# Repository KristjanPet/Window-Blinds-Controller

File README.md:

> [!NOTE]
> This is the first hardware version of the project. Both the PCB and mechanical design are relatively bulky; a second revision is in development with the goal of reducing the overall size by approximately 80%.
>
> Contributions, design ideas, and improvement suggestions are more than welcome.

# Window Blinds Controller

ESP32-S3 based embedded controller for motorized window blinds, built with C++/ESP-IDF, TMC2209 stepper control, FreeRTOS event-driven architecture, MQTT integration, custom KiCad PCB, and custom mechanical parts.

## What this project demonstrates

- Embedded C++ architecture using separated modules and interfaces
- ESP32-S3 firmware development with ESP-IDF and PlatformIO
- FreeRTOS task-based design with a central command/event queue
- Stepper motor control using RMT pulse generation and PCNT position tracking
- TMC2209 UART driver configuration and DIAG/stall event handling
- Homing, calibration, soft limits, stall recovery, and fault-state handling
- MQTT-based smart-home command interface
- Unit testing with PlatformIO/Unity and fake hardware abstractions
- Custom KiCad schematic and PCB design
- Custom mechanical design: CNC aluminium motor/rope holder and 3D printed enclosure
- Doxygen API documentation
- Project planning using Jira and draw.io diagrams

---

## Hardware

Main components:

| Component | Purpose |
|---|---|
| ESP32-S3 | Main MCU, Wi-Fi, FreeRTOS firmware |
| TMC2209 | Stepper motor driver with UART configuration and DIAG/stall signal |
| Nema 17 Stepper motor | Blind movement |
| NJK-5002C Home/reference sensor | Calibration and homing |
| Wall buttons | Local manual control |
| Custom PCB | Power, MCU, driver, sensor, and connector integration |

## Mechanical design

The project also includes custom mechanical parts:

- CNC aluminium motor and rope holder for the blind mechanism
- 3D printed front/back mounting holders for aluminium
- 3D printed electronics case
- 3D printed cover
- CAD models and exported STL/STEP files

## Documentation and planning

- Doxygen configuration for generated C++ API documentation
- draw.io diagrams for system architecture and firmware flow
- Jira used for task planning, issue tracking, and development organization

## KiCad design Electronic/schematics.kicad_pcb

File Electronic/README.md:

# Electronics Hardware

This folder contains the PCB and electronics design files for the window blinds controller.

The electronics are built around an ESP32-S3 development board, a TMC2209 stepper motor driver, a 12 V to 5 V buck converter, input protection, button/sensor connectors, and dual-inverter Schmitt-trigger input paths.

## Schematics

## Main electronics

| Component                  | Qty | Value / Part                | Purpose                                                                 |
| -------------------------- | --: | --------------------------- | ----------------------------------------------------------------------- |
| ESP32-S3 development board |   1 | `ESP32-S3-DEVKITC-1-N16R8V` | Main MCU, firmware, Wi-Fi, MQTT, GPIO control                           |
| Stepper driver             |   1 | `TMC2209 SilentStepStick`   | Stepper motor driver with UART configuration and DIAG/StallGuard output |
| Buck converter             |   1 | 12 V to 3 V DC-DC buck      | Generates 3 V supply from the 12 V input                                |
| Schmitt trigger            |   1 | `74HC14`                    | Cleans three input signals with two inverter gates per signal            |
| TVS diode                  |   1 | `SMBJ15A`                   | 12 V input transient protection                                         |
| Polyfuse                   |   1 | 2 A                         | Input overcurrent protection                                            |

## Passive components

| Component type | Qty | Value  |
| -------------- | --: | ------ |
| Capacitors     |   4 | 100 nF |
| Capacitor      |   1 | 470 µF |
| Resistors      |   2 | 1 kΩ   |
| Resistors      |   3 | 10 kΩ  |
| Resistors      |   3 | 3.3 kΩ |

## Connectors

| Connector    | Qty | Purpose                                           |
| ------------ | --: | ------------------------------------------------- |
| 2-pin JST-XH |   1 | Power input                                       |
| 4-pin JST-XH |   1 | External wiring / motor-driver related connection |
| 3-pin JST-XH |   1 | External input buttons connection                  |
| 3-pin JST-XH |   1 | NJK-5002C home sensor connection                  |

## Conditioned input logic

Each external input passes through two gates of the 74HC14. The two inversions
cancel, so the ESP32-S3 sees the same logical polarity as the signal entering the
first gate. The final gate is a 3.3 V push-pull output, so the firmware keeps the
ESP32 internal pull resistors disabled.

| Input       | ESP32-S3 pin | Pre-Schmitt idle | Pre-Schmitt active | ESP32 idle | ESP32 active | Activation edge |
| ----------- | -----------: | ---------------: | -----------------: | ---------: | -----------: | --------------: |
| Up button   |     `GPIO12` |              LOW |               HIGH |        LOW |          HIGH |          Rising |
| Down button |     `GPIO13` |              LOW |               HIGH |        LOW |          HIGH |          Rising |
| Home sensor |     `GPIO14` |             HIGH |                LOW |       HIGH |           LOW |         Falling |

## External hardware

The PCB is designed to work with the following external hardware:

| Part                                           | Notes                                                |
| ---------------------------------------------- | ---------------------------------------------------- |
| 12 V, 3 A power supply adapter                 | Main power input for the controller and motor system |
| NEMA 17 stepper motor `17HS4401`               | Stepper motor used to drive the blinds mechanism     |
| GREATZT NJK-5002C Hall effect proximity sensor | Home/reference sensor for calibration                |

Before choosing the motor and power supply, the weight and friction of the specific blinds should be checked. Heavier blinds, tight mechanisms, or higher-friction rope systems may require more torque, different gearing, or a stronger motor/driver setup.

## Design notes

The current PCB uses development-board style modules for the ESP32-S3, TMC2209 SilentStepStick, and DC-DC buck converter.

This made the prototype easier to build and debug because those modules were available during development. If space is critical, these modules could be replaced with direct SMD implementations in a future PCB revision.

Possible future optimizations:

* replace ESP32-S3 DevKit with the ESP32-S3 module (or any other not so overpowerd ESP) directly on the PCB
* replace TMC2209 SilentStepStick with the bare TMC2209 IC and required support components
* replace the buck converter module with an onboard SMD regulator circuit
* reduce connector size or move connectors based on the final enclosure
* optimize PCB shape for the mechanical case

## Safety note

This board controls a motorized mechanism. Before installation, verify:

* correct supply voltage and polarity
* current rating of the power adapter
* stepper motor current settings
* fuse/protection behavior
* connector wiring
* home sensor behavior
* motor direction
* stall detection
* mechanical end stops

Do not operate the blinds unattended until calibration, stall detection, and fault handling have been tested on the real mechanism.

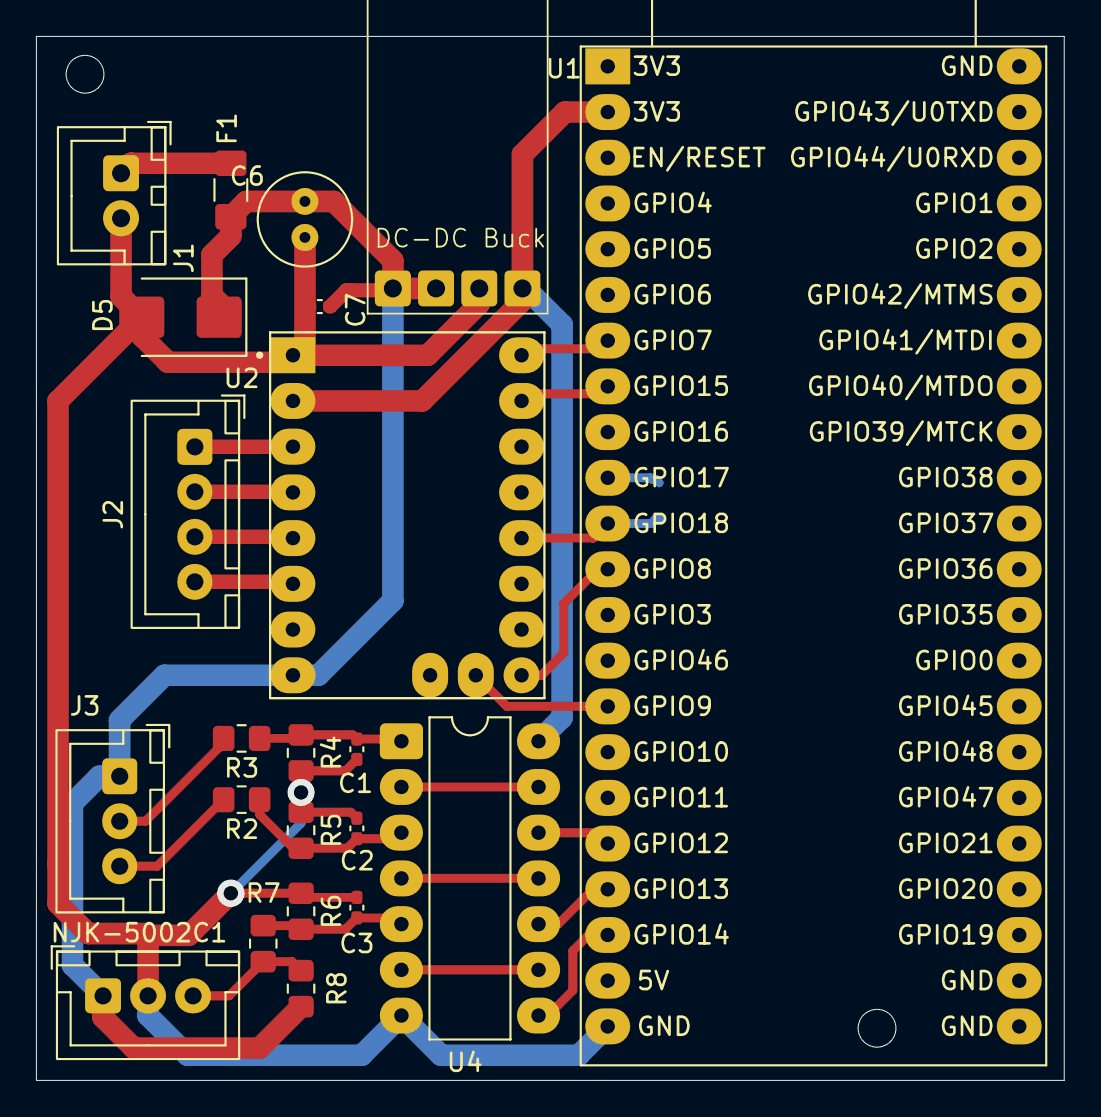
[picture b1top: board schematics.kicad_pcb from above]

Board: 2 copper layers, 57.1 x 58.0 mm, 23 parts (1 on the bottom side), 26 nets.

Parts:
C1, C2, C3, C7: 100nF; C_0402_1005Metric_Pad0.74x0.62mm_HandSolder
C6: 470uF; C_Radial_D5.0mm_H7.0mm_P2.00mm
D5: SMBJ15A; D_SMB
F1: Polyfuse 2A; Fuse_1206_3216Metric_Pad1.42x1.75mm_HandSolder
J1: Jack-DC; JST_XH_B2B-XH-A_1x02_P2.50mm_Vertical
J2: Conn_01x04_Socket; JST_XH_B4B-XH-A_1x04_P2.50mm_Vertical
J3: Conn_01x03; JST_XH_B3B-XH-A_1x03_P2.50mm_Vertical
NJK-5002C1: JST_XH_B3B-XH-A_1x03_P2.50mm_Vertical
R1, R8: 1k; R_0805_2012Metric_Pad1.20x1.40mm_HandSolder
R2, R3, R7: 10k; R_0805_2012Metric_Pad1.20x1.40mm_HandSolder
R4, R5, R6: 3.3k; R_0805_2012Metric_Pad1.20x1.40mm_HandSolder
U1: ESP32-S3-DEVKITC-1-N16R8V; ESP32-S3-DevKitC
U2: TMC2209_SILENTSTEPSTICK; MODULE_TMC2209_SILENTSTEPSTICK
U3: DC-DC 12V-3V buck; DC-DC-Buck-converter-12V-5V
U4: 74HC14; DIP-14_W7.62mm_LongPads

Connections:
3V3: U1.1 (3V3), U2.2 (VIO), U3.3 (Vout), U4.14 (VCC)
GND: C1.1, C2.1, C3.1, C6.2, C7.2, D5.2 (A2), J1.2, NJK-5002C1.2 (GND), R4.2, R5.2, R6.2, U1.22 (GND), U2.1 (GND), U2.7 (GND), U3.2 (GND), U4.7 (GND)
unnamed: C1.2, R3.1, R4.1, U4.1
unnamed: C2.2, R2.1, R5.1, U4.3
unnamed: C3.2, R6.1, R7.2, U4.5
unnamed: J3.3, R2.2
unnamed: J3.2, R3.2
unnamed: NJK-5002C1.3 (DATA), R7.1, R8.2
unnamed: C6.1, C7.1, D5.1 (A1), F1.1, J3.1, NJK-5002C1.1 (VCC), R8.1, U2.8 (VM), U3.1 (Vin), U3.4 (EN)
unnamed: F1.2, J1.1
unnamed: J2.2 (Pin_1), U2.4 (M1A)
unnamed: J2.3 (Pin_2), U2.5 (M2A)
unnamed: J2.1 (Pin_3), U2.3 (M1B)
unnamed: J2.4, U2.6 (M2B)
unnamed: U1.7 (GPIO7), U2.9 (DIR)
unnamed: U1.12 (GPIO8), U2.16 (~EN)
unnamed: U1.15 (GPIO9), U2.18 (DIAG)
unnamed: U1.18 (GPIO12), U4.12
unnamed: U1.19 (GPIO13), U4.10
unnamed: U1.20 (GPIO14), U4.8
unnamed: U1.8 (GPIO15), U2.10 (STEP)
unnamed: R1.1, U1.10 (GPIO17)
unnamed: R1.2, U1.11 (GPIO18), U2.13 (UART)
unnamed: U4.6, U4.9
unnamed: U4.4, U4.11
unnamed: U4.2, U4.13

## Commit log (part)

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2026-03-11 Add initial README for Window-Blinds-Controller project
    Added initial project documentation for the Window-Blinds-Controller, outlining project goals, status, planned features, hardware notes, development approach, repository goals, and initial task list.
2026-03-13 Add hardware wiring scheme to README
    Added hardware wiring scheme section with schematics image.
    Starting with TMC2209 stepper motor driver and wall switches.
2026-03-14 Added images and schematics
    Added images for easier schematics update.
    Updated resistor divider at wall switches
2026-03-15 Update schematics.png
    Added RC fillter and schmitt trigger to reduse noise
2026-03-16 Update schematics.png
    Added NJK-5002C1 proximity sensor
2026-03-17 Init platformio project
2026-03-17 Added build_falgs
2026-03-17 Motor driver POC
2026-03-17 Setup controll buttons GPIO
2026-03-18 Detect button press
2026-03-18 Update button controll by using timer
2026-03-18 Updated button handeling by using queue and seperet task
2026-03-19 POC of controlling motor via buttons
2026-03-19 Updated schematics - add bulk cap at motor driver
2026-03-21 Cleaned unused stuff
2026-03-21 Added blindsController header and entities
2026-03-21 Added BlindsController methods
2026-03-22 Added motorControll class
2026-03-22 Moved motor pins & gptimer init to motor class
2026-03-23 Added stepTimerCallback method
2026-03-23 Added methods for motor controll up/down
2026-03-23 Implement MotorController class in main.cpp
2026-03-23 Added ButtonHandler class
2026-03-23 Added init to ButtonHandler
2026-03-24 Added ISR button handler
2026-03-24 Added buttonTask & MotorController entity to ButtonHandler
2026-03-24 Implemented ButtonHandler class into main
2026-03-24 Added stopMotor function in MotorController
2026-03-24 Fix motor moving logic
2026-03-24 Added error handeling
2026-03-24 Added motorState
2026-03-25 Cleanup includes
2026-03-25 Added Types with movecommand enum class
2026-03-26 Moved motor controll logic out of buttonhandler
2026-03-26 Added BlindsController for controlling motor logic
2026-03-26 Added motor controll logic To Blinds controller
2026-03-26 Updated blinds command logic
2026-03-26 Updated ButtonHandler to use blinds class - updated buttonTask button logic
2026-03-26 Fixed overflow problem
2026-03-26 Added error handling to sendCommand
2026-03-26 Ignore up/down commands if blinds are fault
2026-03-26 Added logging error in case of false sendCommand
2026-03-27 Updated BlindsController sendComand - renamed to handleCommand - motorController get by reference insted of pointer - If state is Fault it stays fault - in case of fault state we get invalid state er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
2026-03-27 Added IMotor interface
2026-03-27 Added getState to blindscontroller
2026-03-28 Added fakeMotor class header for testing
2026-03-28 Updated FakeMotor methods
2026-03-28 Added motor unit test
2026-03-28 Added toglle up/down test
2026-03-28 Added motor failure test
2026-03-28 Added fault bilnds state tests
2026-03-28 Added stop tests
2026-03-28 Added same button toggle test
2026-03-28 and also for down
2026-03-28 Added some other tests
2026-03-28 Added step counting
2026-03-29 Added soft limit temporary replacing sensors - stepTimer counts steps and notify task - Task stops the gptimer on limit
2026-03-29 Added stop error handeling
2026-03-29 Renamed BlindsEvent shared type - added LIMIT_REACHED
2026-03-29 Added new switch case and change handleCommand method to task
2026-03-30 Implemented queue for motor commands
2026-03-30 Implemented queue sender to Buttonhandler
2026-03-30 Added commands queue in MotorController - for informing on limit reached
2026-03-30 Moved commandsQueueHandle to privet and added shared method for sending
2026-03-31 Added blindsCommandQueue transporter
2026-03-31 Implement queue transporter in BlindsController
2026-03-31 Implemented command queue transporter to MotorController
2026-03-31 Implemented commands queue transporter into ButtonHandler
2026-04-01 Seperete logic from task for simpler testing
2026-04-01 Updated unit tests
2026-04-01 Fixed test error
2026-04-02 Added critical section to shared states in MotorController
2026-04-02 Main and Button error handleing improved
2026-04-02 Add missing queue create check
2026-04-02 Clean up the code
2026-04-02 Error handeling fix
2026-04-02 Added small application config layer for constants - improved const hygiene
2026-04-02 Added tmc2209Driver class - init uart config
2026-04-03 Testing drivers UART comm
2026-04-04 Seting POC step resolution via UART
2026-04-21 Set motor current level on hold, run and delay
2026-04-21 Refactor Tmc2209Driver to use constants for UART configuration and improve error handling
2026-04-22 Fine tune motor driver settings
2026-04-22 Add SG_RESULT register handling and logging task to Tmc2209Driver
2026-04-22 Updated Tmc2209Driver with DIAG pin handling and ISR integration; update configuration parameters for stall guard and UART driver pins
2026-04-23 Update TMC2209 configuration parameters
2026-04-23 Refactor LIMIT_REACHED handling in BlindsController to improve state management
2026-04-27 Add AGENTS.md for AI coding agent guidelines and project context
2026-04-28 Add HomeSensor class and integrate home sensor functionality
2026-04-29 Implement homing detection and logging in BlindsController + added schmitt trigger
2026-04-30 Refactor MotorController to implement ramping logic
2026-05-01 Enhance BlindsController to manage HOME state and update motor control logic
2026-05-02 Refactor motor control methods in MotorController to use a unified move function and update step handling logic
2026-05-02 Add POC calibration handling to BlindsController and initiate calibration in main
2026-05-07 Refactor BlindsController and MotorController for improved calibration handling and state management
2026-05-08 On limit ignore button press bug fix
2026-05-08 Refactor BlindsController and HomeSensor for sensor check at init POC
2026-05-09 Homing sensor check bugfix
2026-05-09 Enhance motor control with current step retrieval and improve stall detection logic
2026-05-11 Improve error handling in app_main
2026-05-11 improve error handling and state management in BlindsController
2026-05-11 Add timer management in MotorController to improve stop functionality
2026-05-11 Refactor FakeMotor to improve state management and add calibration failure tests
2026-05-11 Enhance BlindsCommandQueue with error handling and dropped event tracking
2026-05-11 Implement recovery event handling in BlindsCommandQueue for dropped events
2026-05-11 Update BlindsController to set state to FAULT on command handling errors and adjust test case naming for clarity
2026-05-12 Add moveToMax method to IMotor and update BlindsController to use it for motor movements
2026-05-12 update tests for new functionality
2026-05-13 Update handleCommand to set state to FAULT during calibration errors
2026-05-13 Add tests for fault state during calibration events in BlindsController
2026-05-14 Implement normal stall recovery in BlindsController
2026-05-14 Add tests for stall recovery scenarios in BlindsController
2026-05-14 Refactor BlindsController to consider target step not just max & min
2026-05-14 Update stall recovery test to verify target step and move call counts
2026-05-14 Add stall recovery handling while calibrating
2026-05-14 Add tests for home calibration stall recovery scenarios
2026-05-16 Initialize calibrationReturnStep_ for improved calibration handling
2026-05-16 Add tests for calibration return handling and fault scenarios
2026-05-16 Refactor BlindsEvent enum for improved readability and organization
2026-05-17 Update schematics image
2026-05-18 Fix button handler configuration and logic for Schmitt trigger
2026-05-19 Add initial Wifi connection implementation files
2026-05-20 Temporary implement WiFi connection and scanning functionality
2026-05-20 Refactor WiFi connection handling and add WifiSecrets example
2026-05-20 Refactor MotorController to implement RMT and PCNT functionality, removing timer-based logic
2026-05-20 Refactor MotorController to improve RMT transaction handling and position calculation
2026-05-20 Updated Wifi class with event handling and connection state management
2026-05-21 Implement MQTT client functionality and update connection secrets management
2026-05-21 Add command handling to MqttClient for blinds control
2026-05-22 Implement percentage-based control for blinds and enhance MQTT command parsing
2026-05-25 Update offsetOfMinStep in AppConfig to improve home detection accuracy
2026-05-26 Added FaultHandler class to manage fault states and records.
2026-05-26 Add fault handling tests to improve robustness of BlindsController
2026-06-01 Add build directory to .gitignore
2026-06-02 Enhance MqttClient for status reporting
2026-06-02 Add tests for FaultHandler notifications and MQTT payloads
2026-06-03 Update schematics image - moved diodes - removed unnecessary capacitors
2026-06-04 Add unit tests for FaultHandler, MotorController, and MqttClient
    - Implemented tests for FaultHandler to verify fault recording and notification behavior.
    - Removed outdated test cases from test_motor_controller.cpp and created a new test file for MotorController.
    - Added tests for MotorController to ensure it rejects invalid movement targets.
    - Created a new test file for MqttClient, including tests for MQTT payload parsing and fault status payload generation.
2026-06-05 Switched from ESP32-U to S3 becouse of internal wifi antena and refactor GPIO pins
2026-06-05 Refactor main.cpp to initialize handlers and controllers as static variables
2026-06-07 Update schematics image to reflect recent design changes
2026-06-08 Update schematics image - Wrong wiring on R6
2026-06-09 Refactor build flags in platformio.ini for optimized compilation
2026-06-09 Update build and test commands in AGENTS.md for ESP32-S3 environment
2026-06-10 Implement Doxyfile for generating documentation
2026-06-11 Update Doxyfile
2026-06-11 Add 'docs/' to .gitignore
2026-06-11 Update schematics image - increase capacitor at power input - added 100uF & 100nF capacitor at TMC driver
2026-06-12 Refactor MotorController documentation and add missing method descriptions
2026-06-12 Update Doxyfile input and exclude paths for improved documentation generation
2026-06-14 Enhance HomeSensor documentation with detailed method descriptions and usage notes
2026-06-15 Enhance IMotor and Tmc2209Driver documentation with detailed method descriptions and usage notes
2026-06-15 Enhance documentation across multiple headers with detailed descriptions for configuration, fault handling, event types, and connection secrets
2026-06-15 Enhance MqttClient and Wifi documentation with detailed method descriptions and usage notes
2026-06-15 Enhance documentation for BlindsCommandQueue, BlindsController and ButtonHandler with detailed method descriptions and usage notes
2026-06-23 Refine project overview and goals in README.md for clarity and conciseness
2026-06-25 Added project structure to Readme
2026-06-25 Moved project structure to inner directory
